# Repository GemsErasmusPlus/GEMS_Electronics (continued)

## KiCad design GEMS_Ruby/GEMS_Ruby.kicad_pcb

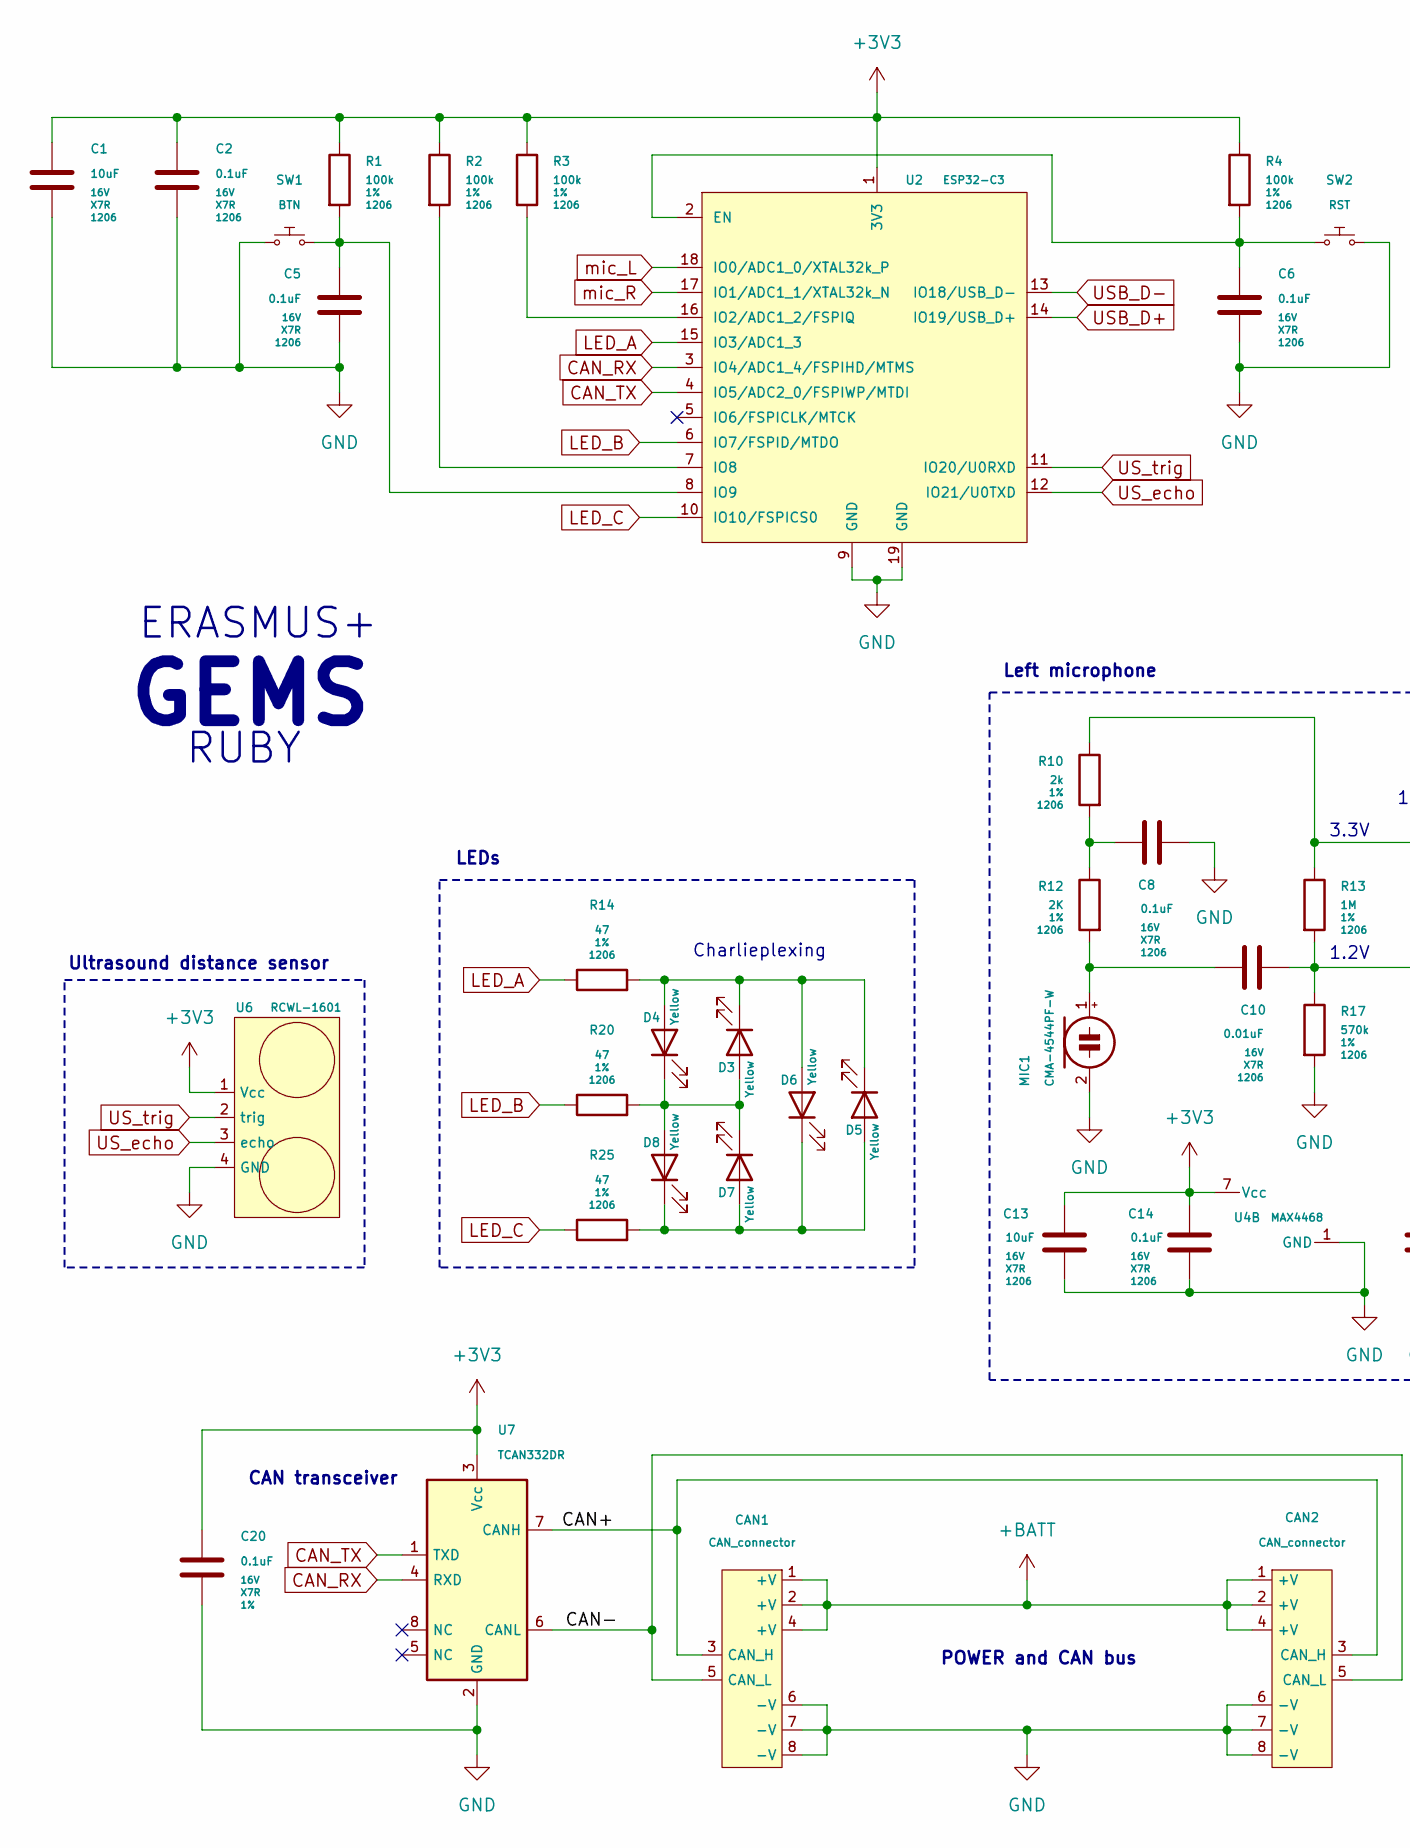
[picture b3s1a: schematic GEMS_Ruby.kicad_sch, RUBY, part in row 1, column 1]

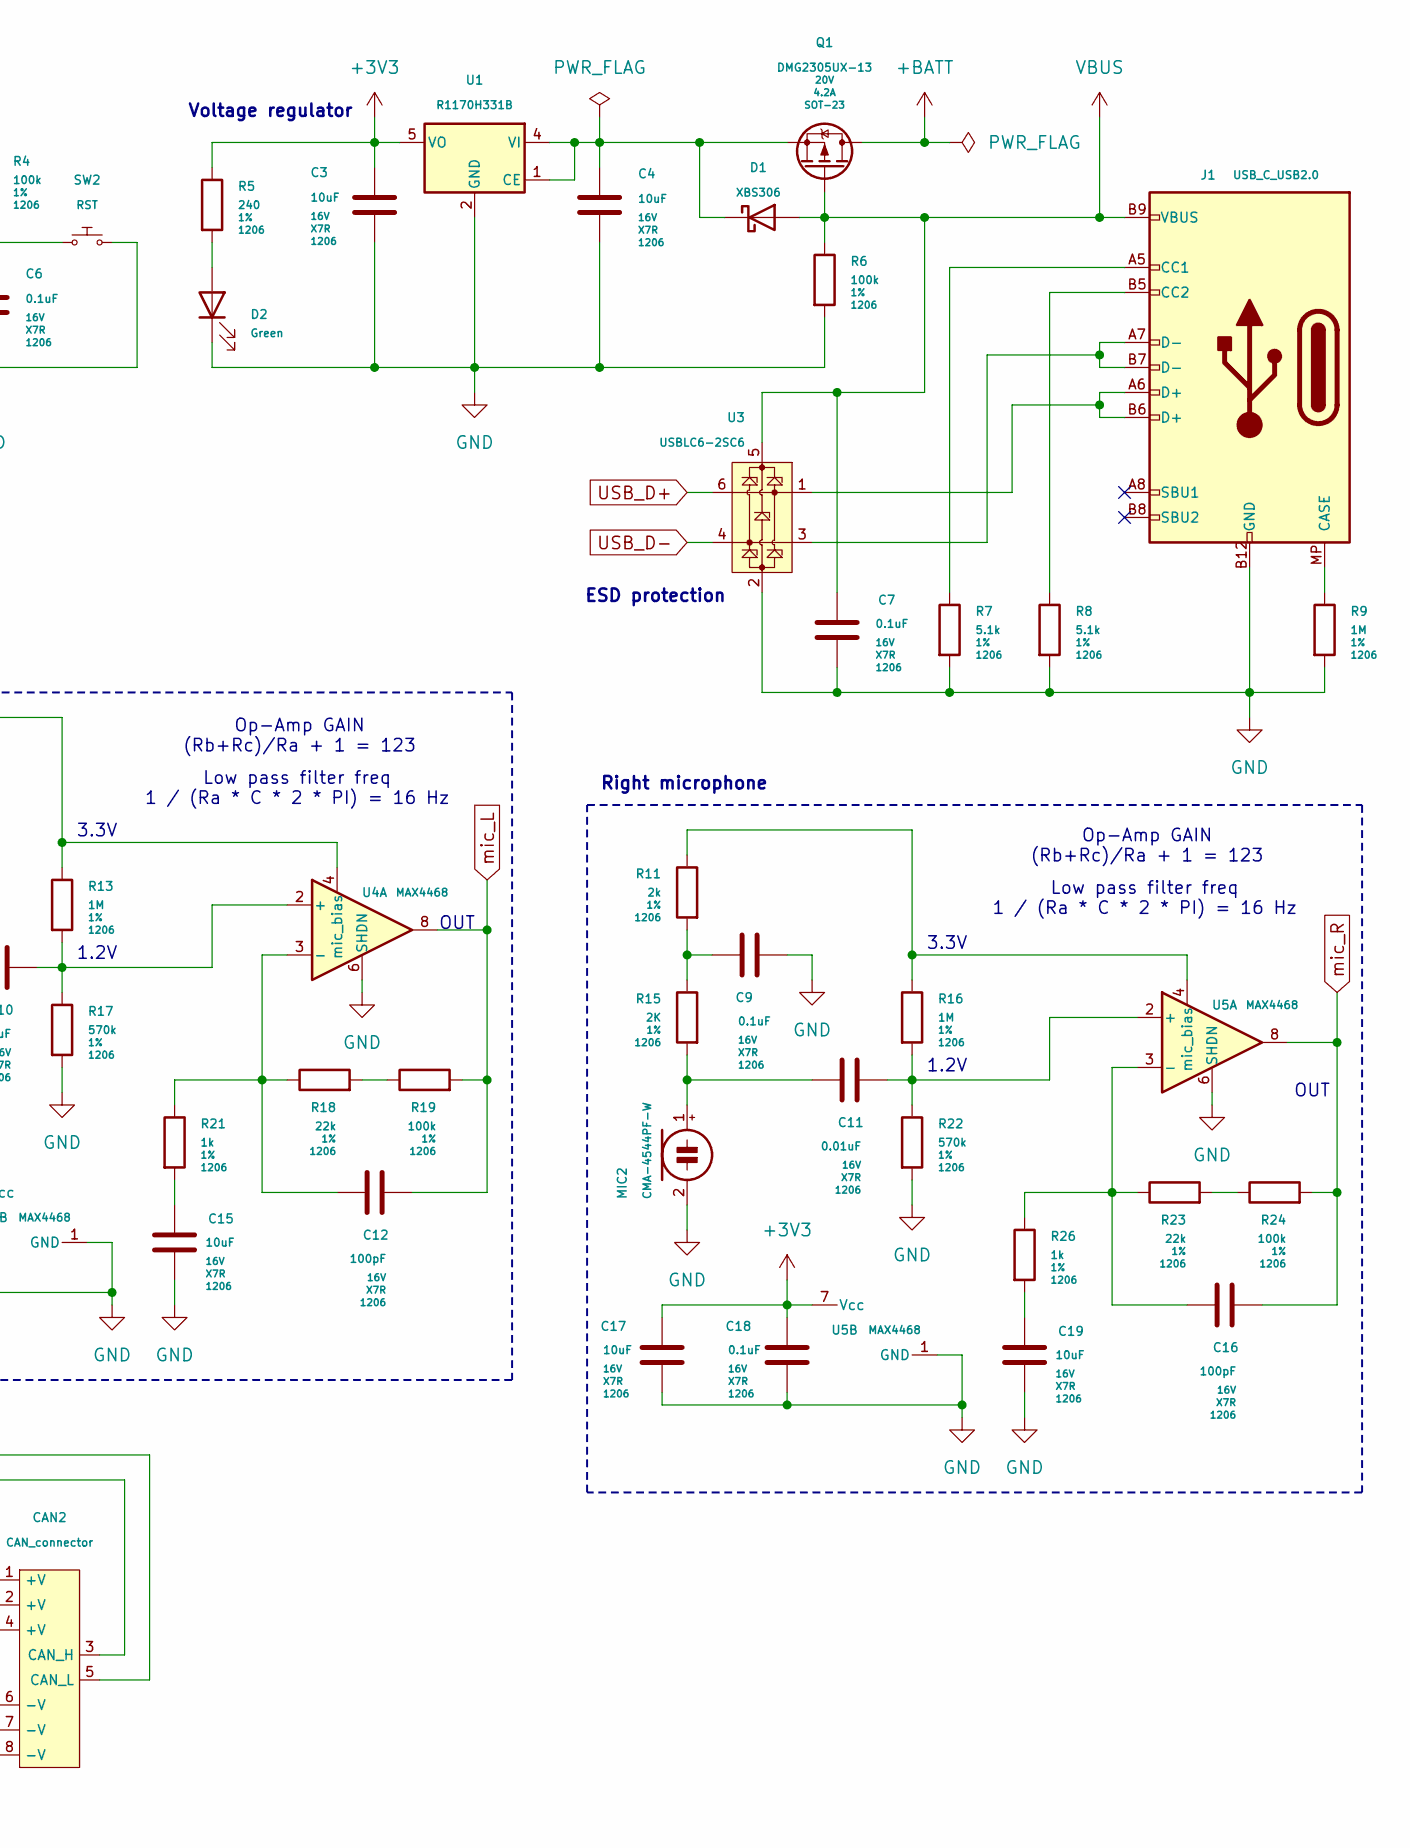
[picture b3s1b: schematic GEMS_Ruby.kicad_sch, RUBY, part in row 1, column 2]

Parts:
C1, C3, C4, C13, C15, C17, C19: 10uF; C_1206_(3216); Voltage 16V; Tolerance X7R
C2, C5, C6, C7, C8, C9, C14, C18, C20: 0.1uF; C_1206_(3216); Voltage 16V; Tolerance X7R
C10, C11: 0.01uF; C_1206_(3216); Voltage 16V; Tolerance X7R
C12, C16: 100pF; C_1206_(3216); Voltage 16V; Tolerance X7R
CAN1, CAN2: CAN_connector; IDC8_Micro-MaTch
D1: XBS306; DO-214_(SMA); Voltage 60V
D2: Green; LED_D3.0mm
D3, D4, D5, D6, D7, D8: Yellow; LED_D3.0mm
J1: USB_C_USB2.0; USB-C_MOLEX-216990-0001
MIC1, MIC2: CMA-4544PF-W
Q1: DMG2305UX-13; SOT-23; Voltage 20V
R1, R2, R3, R4, R6, R19, R24: 100k; R_1206_(3216); Tolerance 1%
R5: 240; R_1206_(3216); Tolerance 1%
R7, R8: 5.1k; R_1206_(3216); Tolerance 1%
R9, R13, R16: 1M; R_1206_(3216); Tolerance 1%
R10, R11: 2k; R_1206_(3216); Tolerance 1%
R12, R15: 2K; R_1206_(3216); Tolerance 1%
R14, R20, R25: 47; R_1206_(3216); Tolerance 1%
R17, R22: 570k; R_1206_(3216); Tolerance 1%
R18, R23: 22k; R_1206_(3216); Tolerance 1%
R21, R26: 1k; R_1206_(3216); Tolerance 1%
SW1: BTN; SW_PUSH_6mm_SMD
SW2: RST; SW_PUSH_6mm_SMD
U1: R1170H331B; SOT-89-5
U2: ESP32-C3; ESP32-C3-WROOM-02
U3: USBLC6-2SC6; SOT-23-6
U4, U5: MAX4468; SOT-23-8
U6: RCWL-1601
U7: TCAN332DR; SOIC-8

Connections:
+3V3: C1.1, C2.1, C3.1, C13.2, C14.2, C17.2, C18.2, C20.1, R1.1, R2.1, R3.1, R4.1, R5.1, U1.5 (VO), U2.1 (3V3), U4.7 (Vcc), U5.7 (Vcc), U6.1 (Vcc), U7.3 (Vcc)
+BATT: CAN1.1 (+V), CAN1.2 (+V), CAN1.4 (+V), CAN2.1 (+V), CAN2.2 (+V), CAN2.4 (+V), Q1.3 (D)
/CAN+: CAN1.3 (CAN_H), CAN2.3 (CAN_H), U7.7 (CANH)
/CAN-: CAN1.5 (CAN_L), CAN2.5 (CAN_L), U7.6 (CANL)
CAN_RX: U2.3 (IO4/ADC1_4/FSPIHD/MTMS), U7.4 (RXD)
CAN_TX: U2.4 (IO5/ADC2_0/FSPIWP/MTDI), U7.1 (TXD)
GND: C1.2, C2.2, C3.2, C4.2, C5.2, C6.2, C7.2, C8.1, C9.1, C13.1, C14.1, C15.2, C17.1, C18.1, C19.2, C20.2, CAN1.6 (-V), CAN1.7 (-V), CAN1.8 (-V), CAN2.6 (-V), CAN2.7 (-V), CAN2.8 (-V), D2.K, J1.A1 (GND), J1.A12 (GND), J1.B1 (GND), J1.B12 (GND), MIC1.2 (-), MIC2.2 (-), R6.2, R7.2, R8.2, R9.2, R17.2, R22.2, SW1.NO, SW2.COM, U1.2 (GND), U2.9 (GND), U2.19 (GND), U3.2 (GND), U4.1 (GND), U4.6 (SHDN), U5.1 (GND), U5.6 (SHDN), U6.4 (GND), U7.2 (GND)
LED_A: R14.1, U2.15 (IO3/ADC1_3)
LED_B: R20.1, U2.6 (IO7/FSPID/MTDO)
LED_C: R25.1, U2.10 (IO10/FSPICS0)
unnamed: C8.2, R10.2, R12.1
unnamed: C9.2, R11.2, R15.1
unnamed: C15.1, R21.2
unnamed: C19.1, R26.2
unnamed: D2.A, R5.2
unnamed: D3.A, D4.K, D7.K, D8.A, R20.2
unnamed: D3.K, D4.A, D5.K, D6.A, R14.2
unnamed: D5.A, D6.K, D7.A, D8.K, R25.2
unnamed: J1.MP (CASE), R9.1
unnamed: J1.A5 (CC1), R7.1
unnamed: J1.B5 (CC2), R8.1
unnamed: J1.A6 (D+), J1.B6 (D+), U3.1 (I/O1)
unnamed: J1.A7 (D-), J1.B7 (D-), U3.3 (I/O2)
unnamed: C10.1, MIC1.1 (+), R12.2
unnamed: C11.1, MIC2.1 (+), R15.2
unnamed: C4.1, D1.K, Q1.2 (S), U1.1 (CE), U1.4 (VI)
unnamed: R18.2, R19.1
unnamed: R23.2, R24.1
unnamed: C6.1, R4.2, SW2.NO, U2.2 (EN)
unnamed: R3.2, U2.16 (IO2/ADC1_2/FSPIQ)
unnamed: R2.2, U2.7 (IO8)
unnamed: C5.1, R1.2, SW1.COM, U2.8 (IO9)
unnamed: C10.2, R13.2, R17.1, U4.2 (+)
unnamed: C12.1, R18.1, R21.1, U4.3 (-)
unnamed: R10.1, R13.1, U4.4 (mic_bias)
unnamed: C11.2, R16.2, R22.1, U5.2 (+)
unnamed: C16.1, R23.1, R26.1, U5.3 (-)
unnamed: R11.1, R16.1, U5.4 (mic_bias)
USB_D+: U2.14 (IO19/USB_D+), U3.6 (I/O1)
USB_D-: U2.13 (IO18/USB_D-), U3.4 (I/O2)
US_echo: U2.12 (IO21/U0TXD), U6.3 (echo)
US_trig: U2.11 (IO20/U0RXD), U6.2 (trig)
VBUS: C7.1, D1.A, J1.A4 (VBUS), J1.A9 (VBUS), J1.B4 (VBUS), J1.B9 (VBUS), Q1.1 (G), R6.1, U3.5 (VBUS)
mic_L: C12.2, R19.2, U2.18 (IO0/ADC1_0/XTAL32k_P), U4.8
mic_R: C16.2, R24.2, U2.17 (IO1/ADC1_1/XTAL32k_N), U5.8

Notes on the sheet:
Right microphone
ESD protection
3.3V
OUT
1.2V
CAN transceiver
Low pass filter freq 1 / (Ra * C * 2 * PI) = 16 Hz
Ultrasound distance sensor
ERASMUS+
Left microphone
POWER and CAN bus
RUBY
GEMS
Op-Amp GAIN (Rb+Rc)/Ra + 1 = 123
Voltage regulator
LEDs
Charlieplexing

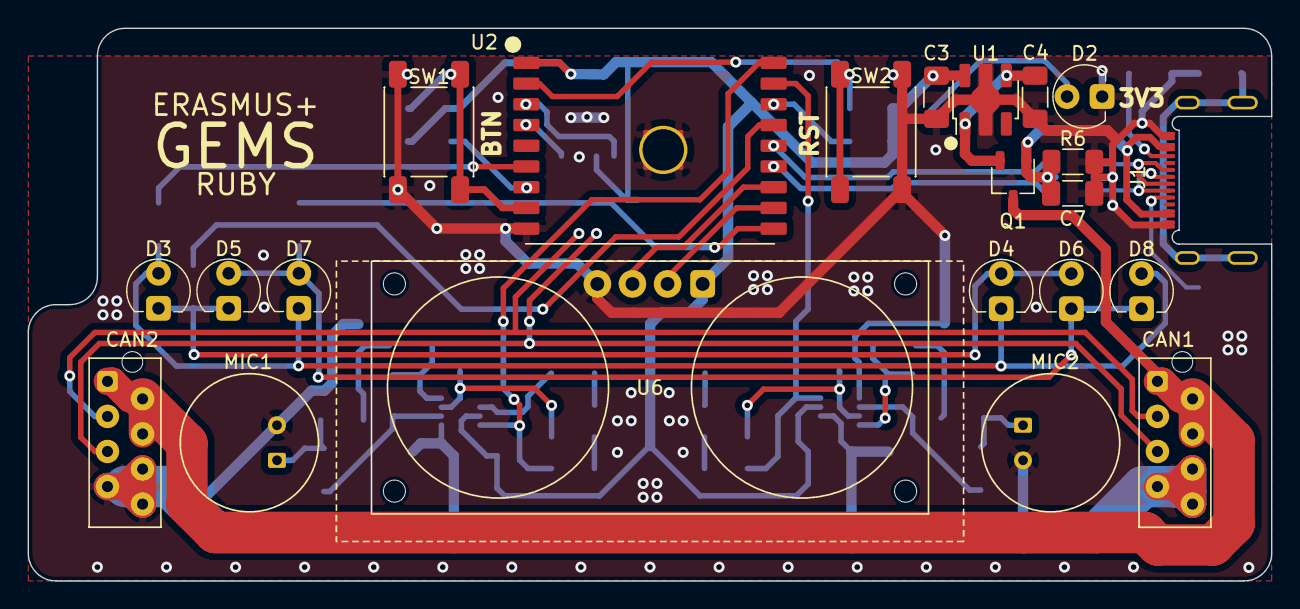
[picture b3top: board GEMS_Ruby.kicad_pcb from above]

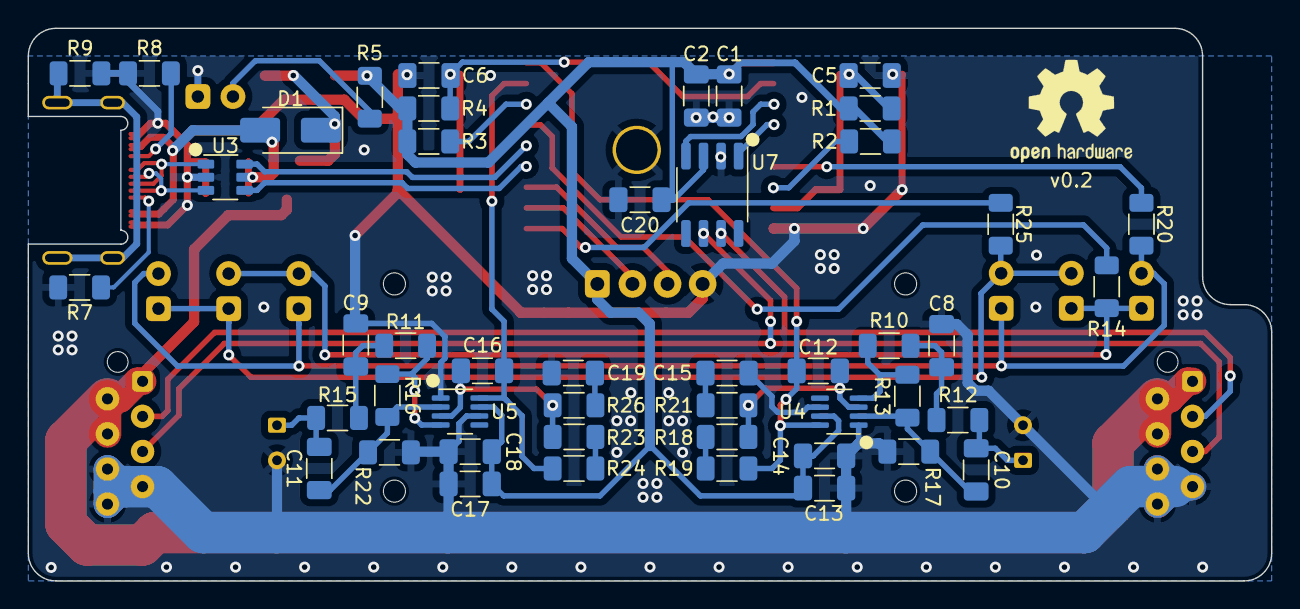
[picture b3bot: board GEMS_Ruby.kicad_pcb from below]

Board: 2 copper layers, 90.0 x 40.0 mm, 69 parts (47 on the bottom side), 45 nets.

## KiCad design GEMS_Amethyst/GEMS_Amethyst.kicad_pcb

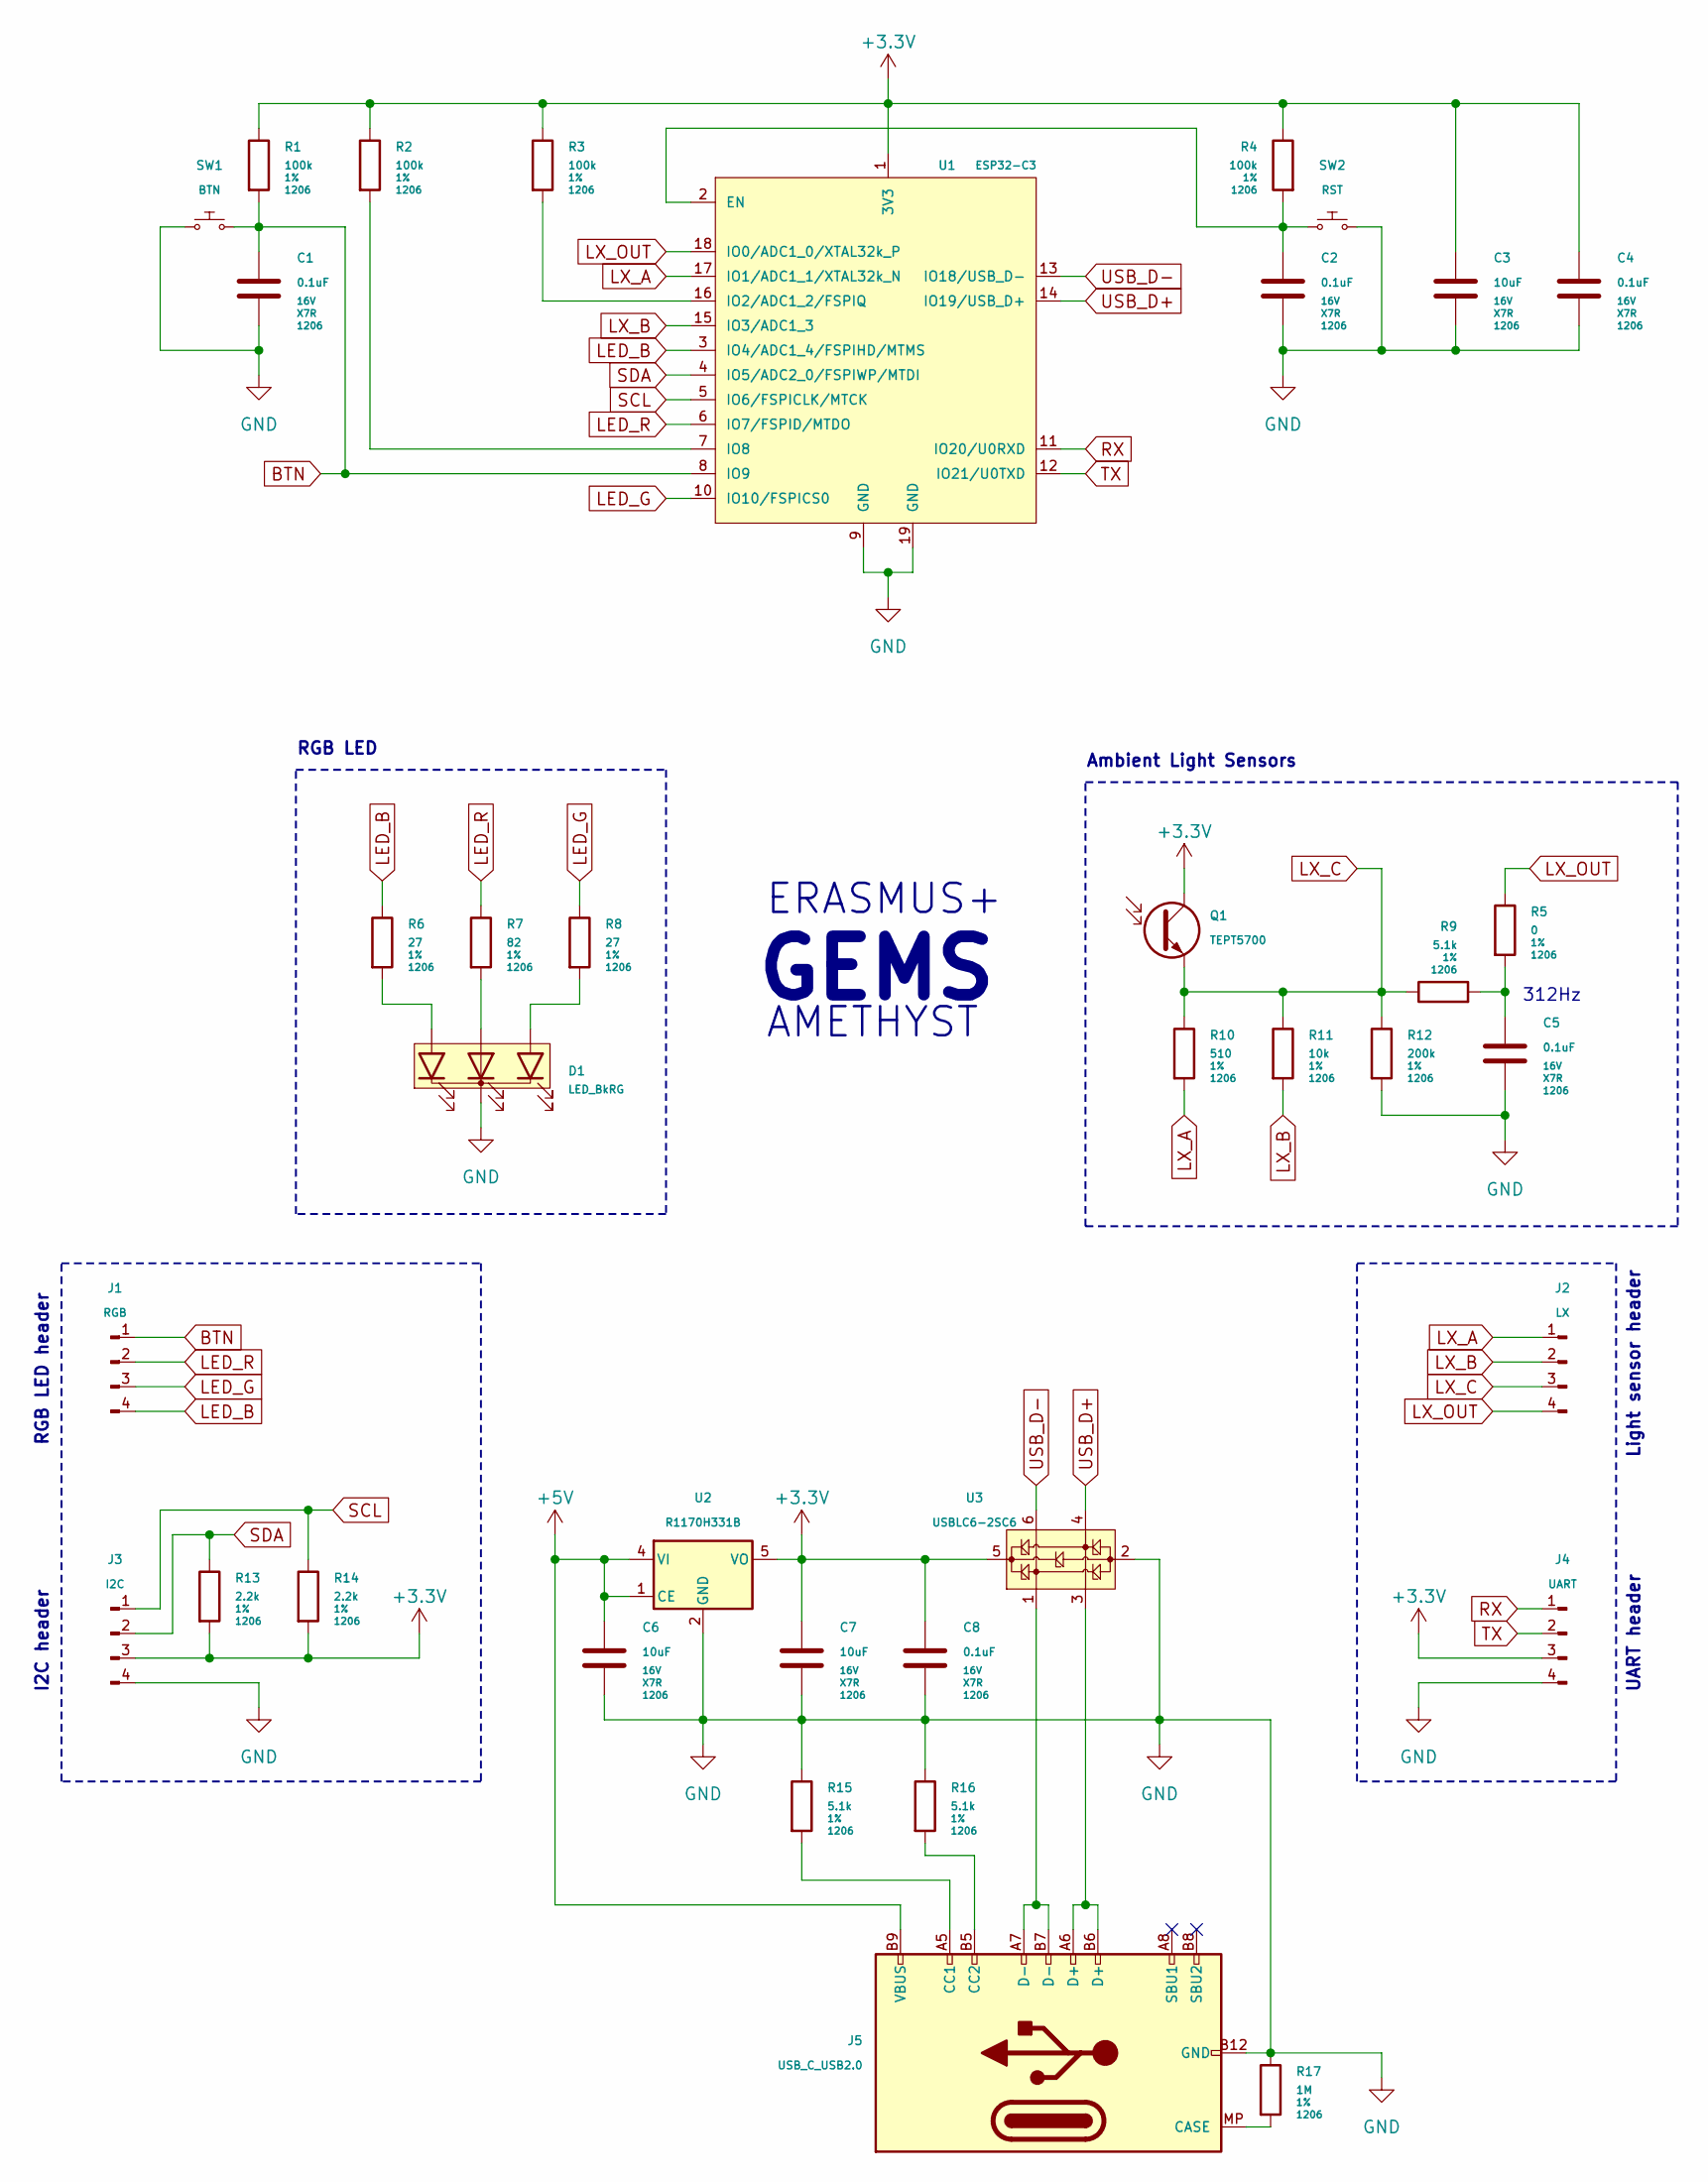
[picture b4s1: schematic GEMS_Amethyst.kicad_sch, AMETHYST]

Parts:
C1, C2, C4, C5, C8: 0.1uF; C_1206_(3216); Voltage 16V; Tolerance X7R
C3, C6, C7: 10uF; C_1206_(3216); Voltage 16V; Tolerance X7R
D1: LED_BkRG; LED_D5.0mm-4_RGB
J1: RGB; PinHeader_1x04_P2.54mm_Vertical
J2: LX; PinHeader_1x04_P2.54mm_Vertical
J3: I2C; PinHeader_1x04_P2.54mm_Vertical
J4: UART; PinHeader_1x04_P2.54mm_Vertical
J5: USB_C_USB2.0; USB-C_MOLEX-216990-0001
Q1: TEPT5700; PT_D5.0mm
R1, R2, R3, R4: 100k; R_1206_(3216); Tolerance 1%
R5: 0; R_1206_(3216); Tolerance 1%
R6, R8: 27; R_1206_(3216); Tolerance 1%
R7: 82; R_1206_(3216); Tolerance 1%
R9, R15, R16: 5.1k; R_1206_(3216); Tolerance 1%
R10: 510; R_1206_(3216); Tolerance 1%
R11: 10k; R_1206_(3216); Tolerance 1%
R12: 200k; R_1206_(3216); Tolerance 1%
R13, R14: 2.2k; R_1206_(3216); Tolerance 1%
R17: 1M; R_1206_(3216); Tolerance 1%
SW1: BTN; SW_PUSH_6mm_SMD
SW2: RST; SW_PUSH_6mm_SMD
U1: ESP32-C3; ESP32-C3-WROOM-02
U2: R1170H331B; SOT-89-5
U3: USBLC6-2SC6; SOT-23-6

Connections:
+3.3V: C3.1, C4.1, C7.1, C8.1, J3.3, J4.3, Q1.C, R1.1, R2.1, R3.1, R4.1, R13.2, R14.2, U1.1 (3V3), U2.5 (VO), U3.5 (VBUS)
+5V: C6.1, J5.A4 (VBUS), J5.A9 (VBUS), J5.B4 (VBUS), J5.B9 (VBUS), U2.1 (CE), U2.4 (VI)
BTN: C1.1, J1.1, R1.2, SW1.COM, U1.8 (IO9)
GND: C1.2, C2.2, C3.2, C4.2, C5.2, C6.2, C7.2, C8.2, D1.K, J3.4, J4.4, J5.A1 (GND), J5.A12 (GND), J5.B1 (GND), J5.B12 (GND), R12.2, R15.1, R16.1, R17.1, SW1.NO, SW2.COM, U1.9 (GND), U1.19 (GND), U2.2 (GND), U3.2 (GND)
LED_B: J1.4, R6.1, U1.3 (IO4/ADC1_4/FSPIHD/MTMS)
LED_G: J1.3, R8.1, U1.10 (IO10/FSPICS0)
LED_R: J1.2, R7.1, U1.6 (IO7/FSPID/MTDO)
LX_A: J2.1, R10.2, U1.17 (IO1/ADC1_1/XTAL32k_N)
LX_B: J2.2, R11.2, U1.15 (IO3/ADC1_3)
LX_C: J2.3, Q1.E, R9.1, R10.1, R11.1, R12.1
LX_OUT: J2.4, R5.1, U1.18 (IO0/ADC1_0/XTAL32k_P)
unnamed: C5.1, R5.2, R9.2
unnamed: D1.Ab (Ablue), R6.2
unnamed: D1.Ag (Agreen), R8.2
unnamed: D1.Ar (Ared), R7.2
unnamed: J5.MP (CASE), R17.2
unnamed: J5.A5 (CC1), R15.2
unnamed: J5.B5 (CC2), R16.2
unnamed: J5.A6 (D+), J5.B6 (D+), U3.3 (I/O2)
unnamed: J5.A7 (D-), J5.B7 (D-), U3.1 (I/O1)
unnamed: C2.1, R4.2, SW2.NO, U1.2 (EN)
unnamed: R3.2, U1.16 (IO2/ADC1_2/FSPIQ)
unnamed: R2.2, U1.7 (IO8)
RX: J4.1, U1.11 (IO20/U0RXD)
SCL: J3.1, R14.1, U1.5 (IO6/FSPICLK/MTCK)
SDA: J3.2, R13.1, U1.4 (IO5/ADC2_0/FSPIWP/MTDI)
TX: J4.2, U1.12 (IO21/U0TXD)
USB_D+: U1.14 (IO19/USB_D+), U3.4 (I/O2)
USB_D-: U1.13 (IO18/USB_D-), U3.6 (I/O1)

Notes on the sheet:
GEMS
RGB LED header
UART header
RGB LED
AMETHYST
Ambient Light Sensors
312Hz
ERASMUS+
Light sensor header
I2C header

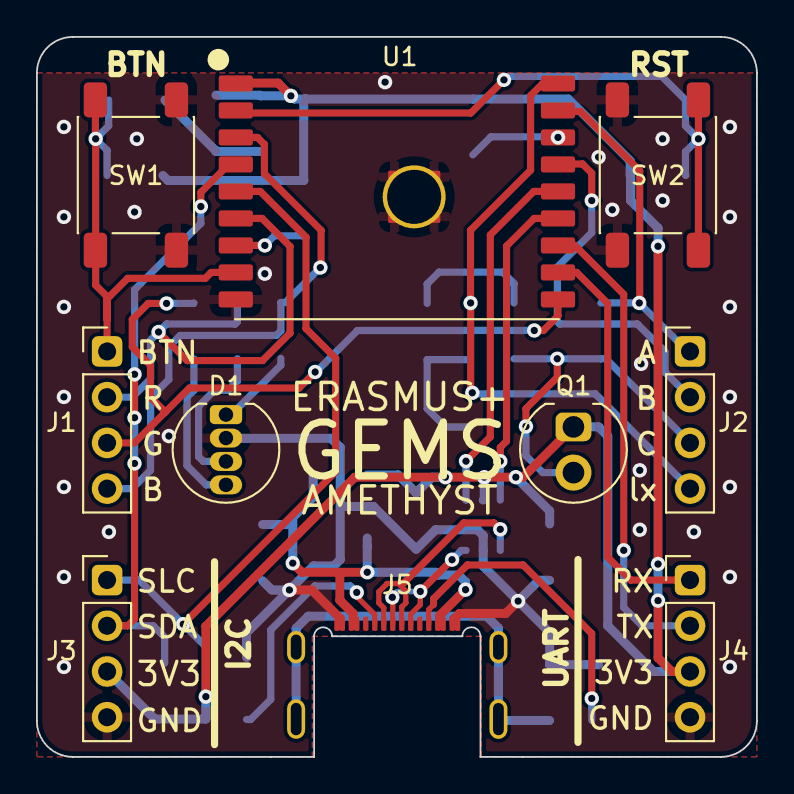
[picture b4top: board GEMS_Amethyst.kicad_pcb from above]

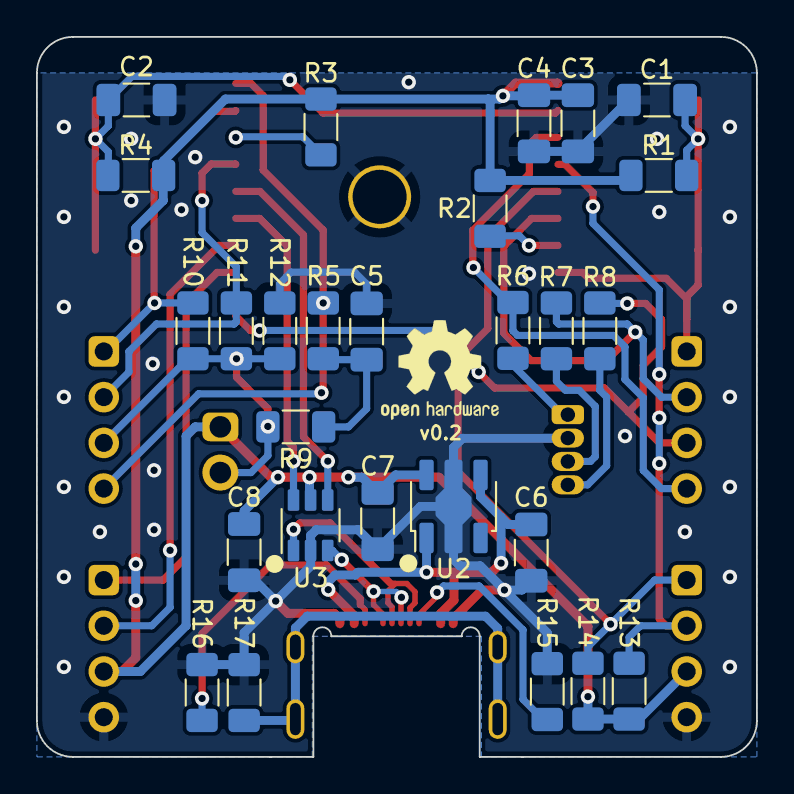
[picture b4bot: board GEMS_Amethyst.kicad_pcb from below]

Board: 2 copper layers, 40.0 x 40.0 mm, 37 parts (27 on the bottom side), 29 nets.

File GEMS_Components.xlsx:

Reference | Value | Tolerance | Voltage | Footprint | Suplier1 | Suplier1 no. | Suplier1M no. | Suplier2 | Suplier2 no. | Suplier2M no. | Qty
C1,C2,C4,C5,C8 | 0.1uF | X7R | 16V | GEMS_library:C_1206_(3216) | Mouser | 603-CC126MRX7R9BB104 |  | ~ | ~ |  | 5
C3,C6,C7 | 10uF | X7R | 16V | GEMS_library:C_1206_(3216) | Mouser | 603-CC126KKX7R7BB106 |  | ~ | ~ |  | 3
D1 | LED_BkRG |  |  | GEMS_library:LED_D5.0mm-4_RGB | Mouser | 743-HV-5RGB60 |  | DigiKey | 1830-1014-ND |  | 1
J5 | USB_C_USB2.0 |  |  | GEMS_library:USB-C_MOLEX-216990-0001 | Mouser | 538-216990-0001 |  | DigiKey | 900-2169900001TR-ND |  | 1
Q1 | TEPT5700 |  |  | GEMS_library:PT_D5.0mm | Mouser | 782-TEPT5700 |  | DigiKey | 751-1059-ND |  | 1
R1,R2,R3,R4 | 100k | 1% |  | GEMS_library:R_1206_(3216) | Mouser | 603-RC1206FR-10100KL |  | ~ | ~ |  | 4
R5 | 0 | 1% |  | GEMS_library:R_1206_(3216) | Mouser | 603-RC1206FR-070RL |  | ~ | ~ |  | 1
R6,R8 | 27 | 1% |  | GEMS_library:R_1206_(3216) | Mouser | 603-RC1206FR-0727RL |  | ~ | ~ |  | 2
R7 | 82 | 1% |  | GEMS_library:R_1206_(3216) | Mouser | 603-RC1206FR-0782RL |  | ~ | ~ |  | 1
R9,R15,R16 | 5.1k | 1% |  | GEMS_library:R_1206_(3216) | Mouser | 603-RC1206FR-075K1L |  | ~ | ~ |  | 3
R10 | 510 | 1% |  | GEMS_library:R_1206_(3216) | Mouser | 603-RC1206FR-07510RL |  | ~ | ~ |  | 1
R11 | 10k | 1% |  | GEMS_library:R_1206_(3216) | Mouser | 603-RE1206FRE0710KL |  | ~ | ~ |  | 1
R12 | 200k | 1% |  | GEMS_library:R_1206_(3216) | Mouser | 603-RC1206FR-07200KL |  | ~ | ~ |  | 1
R13,R14 | 2.2k | 1% |  | GEMS_library:R_1206_(3216) | Mouser | 603-RC1206FR-072K2L |  | ~ | ~ |  | 2
R17 | 1M | 1% |  | GEMS_library:R_1206_(3216) | Mouser | 603-RC1206FR-071ML |  | ~ | ~ |  | 1
SW1 | BTN |  |  | GEMS_library:SW_PUSH_6mm_SMD | Mouser | 611-PTS645SM50SMTR92 |  | ~ | ~ |  | 1
SW2 | RST |  |  | GEMS_library:SW_PUSH_6mm_SMD | Mouser | 611-PTS645SK50SMTR92 |  | ~ | ~ |  | 1
U1 | ESP32-C3 |  |  | GEMS_library:ESP32-C3-WROOM-02 | Mouser | 356-ESP32C3WROOM02N4 |  | DigiKey | 1965-ESP32-C3-WROOM-02-N4TR-ND |  | 1
U2 | R1170H331B |  |  | GEMS_library:SOT-89-5 | Mouser | 848-R1170H331BT1FE |  | DigiKey | 2129-R1170H331B-T1-FETR-ND |  | 1
U3 | USBLC6-2SC6 |  |  | GEMS_library:SOT-23-6 | Mouser | 511-USBLC6-2SC6 |  | DigiKey | 497-5235-2-ND |  | 1

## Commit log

2025-02-17 Create LICENSE
2025-02-17 added design files of all modules
2025-02-24 readme.md update
2025-03-03 updated Library
